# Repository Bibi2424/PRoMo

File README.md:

# PRoMo

## "Plateforme pour la Robotique Mobile"

### Mobile Robotic Plateform

This project is about creating a mobile robot from scratch.
There are four major parts in this project :

- Mechanics : Build a differential drive plateform with two DC motors with encoders. The different components must be build with Laser cutting and 3D printing (from low cost websites).
			
- Electronics : Create a main board based on a STM32F4 microcontroller with many components like motors, sensors, actuators, RF transmitters...
			
- Firmware : This can go two ways:
	- Provide a sets of high level librairies for controlling a sets of sensors and actuators and example projects, 
	- Give the code as is but with a performant way of interfacing with it (serial communication)

- Documentation : All the informations to understand the project will be there, with some tutorials. At the moment, used to store local datasheets
			
The aim of this projects is to propose some basics to start mobile robotic for the beginners and to simplify things for advanced people.

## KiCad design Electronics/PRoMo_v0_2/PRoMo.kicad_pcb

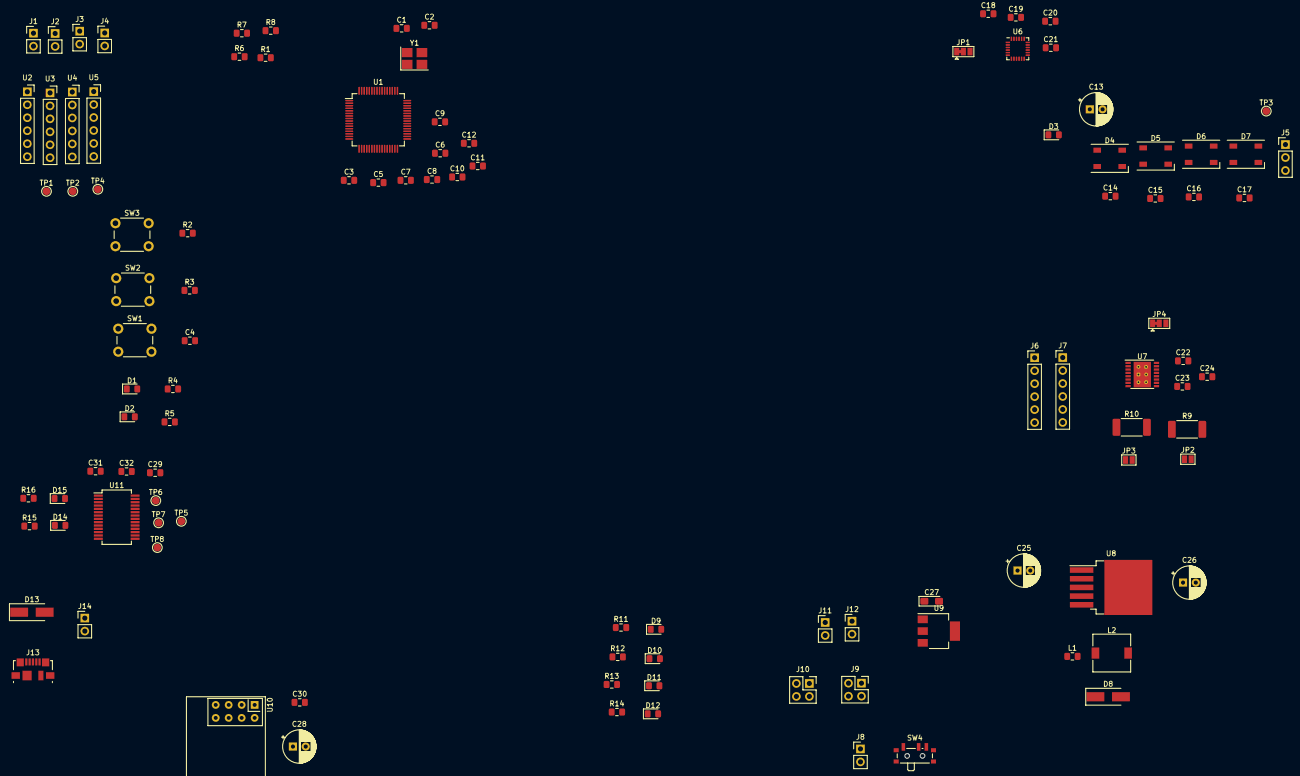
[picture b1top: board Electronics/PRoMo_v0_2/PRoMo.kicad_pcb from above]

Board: 2 copper layers, 111 parts (0 on the bottom side), 76 nets, no tracks yet.

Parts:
C1, C2: 18pF; C_0805_2012Metric_Pad1.15x1.40mm_HandSolder
C3, C4, C5, C7, C8, C9, C12, C14, C15, C16, C17, C19, C20, C29, C31: 100nF; C_0805_2012Metric_Pad1.15x1.40mm_HandSolder
C6, C32: 4.7uF; C_0805_2012Metric_Pad1.15x1.40mm_HandSolder
C10, C24: 10uF; C_0805_2012Metric_Pad1.15x1.40mm_HandSolder
C11: 1uF; C_0805_2012Metric_Pad1.15x1.40mm_HandSolder
C13, C28: 100uF; CP_Radial_D6.3mm_P2.50mm
C18, C22: 10nF; C_0805_2012Metric_Pad1.15x1.40mm_HandSolder
C21: 2.2nF; C_0805_2012Metric_Pad1.15x1.40mm_HandSolder
C23: 2.2uF; C_0805_2012Metric_Pad1.15x1.40mm_HandSolder
C25: 680uF; CP_Radial_D6.3mm_P2.50mm
C26: 220uF; CP_Radial_D6.3mm_P2.50mm
C27: 10uF; CP_EIA-3216-18_Kemet-A_Pad1.58x1.35mm_HandSolder
C30: Unpopulated; C_0805_2012Metric_Pad1.15x1.40mm_HandSolder
D1, D2: LED_Blue; LED_0805_2012Metric_Pad1.15x1.40mm_HandSolder
D3: M7; D_0805_2012Metric_Pad1.15x1.40mm_HandSolder
D4, D5, D6, D7: SK6812; LED_SK6812_PLCC4_5.0x5.0mm_P3.2mm
D8: SS14; D_SMA_Handsoldering
D9: LED_Red; LED_0805_2012Metric_Pad1.15x1.40mm_HandSolder
D10: LED_Yellow; LED_0805_2012Metric_Pad1.15x1.40mm_HandSolder
D11, D12: LED_Green; LED_0805_2012Metric_Pad1.15x1.40mm_HandSolder
D13: D_Zener_Small; D_SMA_Handsoldering
D14, D15: Yellow; LED_0805_2012Metric_Pad1.15x1.40mm_HandSolder
H1, H2, H3, H4: MountingHole; MountingHole_3.2mm_M3
J1, J2, J3, J4, J8, J14: Conn_01x02; PinHeader_1x02_P2.54mm_Vertical
J5: Conn_01x03; PinHeader_1x03_P2.54mm_Vertical
J6: ME_L; PinHeader_1x06_P2.54mm_Vertical
J7: ME_R; PinHeader_1x06_P2.54mm_Vertical
J9, J10: Conn_02x02_Counter_Clockwise; PinSocket_2x02_P2.54mm_Vertical
J11: AUX_IN; PinHeader_1x02_P2.54mm_Vertical
J12: AUX_OUT; PinHeader_1x02_P2.54mm_Vertical
J13: USB_B_Micro; USB_Micro-B_Molex_47346-0001
JP1: SLAVE_ADDR; SolderJumper-3_P1.3mm_Bridged12_Pad1.0x1.5mm
JP2, JP3: SolderJumper_2_Open; SolderJumper-2_P1.3mm_Open_Pad1.0x1.5mm
JP4: SolderJumper_3_Bridged12; SolderJumper-3_P1.3mm_Bridged12_Pad1.0x1.5mm
L1: 22uh; L_0805_2012Metric_Pad1.15x1.40mm_HandSolder
L2: 33uh; L_7.3x7.3_H3.5
R1, R6, R7, R8: 1k; R_0805_2012Metric_Pad1.15x1.40mm_HandSolder
R2, R3: 10k; R_0805_2012Metric_Pad1.15x1.40mm_HandSolder
R4, R5, R14: 47R; R_0805_2012Metric_Pad1.15x1.40mm_HandSolder
R9, R10: Sense; R_2512_6332Metric_Pad1.52x3.35mm_HandSolder
R11: 470R; R_0805_2012Metric_Pad1.15x1.40mm_HandSolder
R12: 330R; R_0805_2012Metric_Pad1.15x1.40mm_HandSolder
R13, R15, R16: 220R; R_0805_2012Metric_Pad1.15x1.40mm_HandSolder
SW1, SW2, SW3: DIP-BUTTON_2P-6.0X3.0X4.3MM_; SW_PUSH_6mm_H5mm
SW4: SW_SPDT; SW_SPDT_PCM12
TP1, TP2, TP3, TP4, TP5, TP6, TP7, TP8: TestPoint; TestPoint_Pad_D1.5mm
U1: STM32F401RETx; LQFP-64_10x10mm_P0.5mm
U2, U3, U4, U5: VL53l0x_breakout; PinSocket_1x06_P2.54mm_Vertical
U6: MPU-6050; InvenSense_QFN-24_4x4mm_P0.5mm
U7: DRV8833PWP; HTSSOP-16-1EP_4.4x5mm_P0.65mm_EP3.4x5mm_Mask2.46x2.31mm_The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
U8: LM2596S-5; TO-263-5_TabPin3
U9: AMS1117-3.3; SOT-223-3_TabPin2
U10: NRF24L01_Breakout; nRF24L01_Breakout
U11: FT232RL; SSOP-28_5.3x10.2mm_P0.65mm
Y1: Crystal_GND24; Crystal_SMD_3225-4Pin_3.2x2.5mm_HandSoldering

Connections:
+3V3: C3.1, C5.1, C7.1, C8.1, C9.2, C10.1, C11.1, C12.1, C18.2, C19.2, C27.1, C28.1, C30.1, J6.3, J7.3, J10.1, J10.2, JP1.3, R1.1, R2.2, R3.2, R4.1, R5.1, R6.1, R7.1, R8.1, R14.2, U1.13, U1.19, U1.32, U1.48, U1.64, U2.1, U3.1, U4.1, U5.1, U6.8, U6.13, U9.2, U10.2
+5V: C13.1, C15.1, C16.1, C17.1, C26.1, C31.2, C32.2, D3.2, D5.3, D6.3, D7.3, J5.1, J9.1, J9.2, J12.2, J14.1, L1.2, L2.2, R13.2, R15.1, R16.1, U8.4, U9.3, U11.4, U11.20
/BOOT1_BP2: R2.1, SW3.1, U1.28
/BP1: R3.1, SW2.1, U1.2
/LED_USR1: D1.1, U1.55
/LED_USR2: D2.1, U1.43
/Motor_driver/ML1: J6.1, U7.2
/Motor_driver/ML2: J6.2, U7.4
/Motor_driver/MR1: J7.1, U7.7
/Motor_driver/MR2: J7.2, U7.5
ADC_ML_SENSE: JP2.2, R9.1, U1.10, U7.3
ADC_MR_SENSE: JP3.2, R10.1, U1.11, U7.6
ADDR_LEDS: D4.2, U1.53
DRV_EN: JP4.1, U1.54
Encoder_L_A: J6.4, U1.56
Encoder_L_B: J6.5, U1.57
Encoder_R_A: J7.4, U1.58
Encoder_R_B: J7.5, U1.59
FTDI_RX: TP6.1, U11.1
FTDI_TX: TP7.1, U11.5
GND: C1.2, C2.2, C3.2, C4.2, C5.2, C6.2, C7.2, C8.2, C10.2, C11.2, C12.2, C13.2, C14.2, C15.2, C16.2, C17.2, C18.1, C19.1, C20.2, C21.2, C23.1, C24.2, C25.2, C26.2, C27.2, C28.2, C29.1, C30.2, C31.1, C32.1, D4.1, D5.1, D6.1, D7.1, D8.2, D9.1, D10.1, D11.1, D12.1, J1.2, J2.2, J3.2, J4.2, J5.3, J6.6, J7.6, J8.1, J9.3, J9.4, J10.3, J10.4, J11.1, J12.1, J13.5, JP1.1, JP2.1, JP3.1, R9.2, R10.2, SW1.1, SW2.2, SW3.2, U1.12, U1.18, U1.31, U1.47, U1.63, U2.2, U3.2, U4.2, U5.2, U6.18, U7.13, U7.17, U8.3, U8.5, U9.1, U10.1, U11.7, U11.18, U11.21, U11.25, Y1.2, Y1.4
I2C_AUX_SCL: R6.2, U1.41
I2C_AUX_SDA: R1.2, U1.40
MPU_INT: U1.8, U6.12
NRF_CE: U1.29, U10.3
NRF_IRQ: U1.9, U10.8
NRF_SPI_MISO: U1.35, U10.7
NRF_SPI_MOSI: U1.36, U10.6
NRF_SPI_SCK: U1.34, U10.5
NRF_nCSN: U1.33, U10.4
NRST: C4.1, JP4.3, SW1.2, U1.7
unnamed: C1.1, U1.5, Y1.1
unnamed: C2.1, U1.6, Y1.3
unnamed: C6.1, U1.30
unnamed: C9.1, U1.1
unnamed: C14.1, D3.1, D4.3
unnamed: C20.1, U6.10
unnamed: C21.1, U6.20
unnamed: C22.1, U7.11
unnamed: C23.2, U7.14
unnamed: C29.2, U11.17
unnamed: D1.2, R4.2
unnamed: D2.2, R5.2
unnamed: D4.4, D5.2
unnamed: D5.4, D6.2
unnamed: D6.4, D7.2
unnamed: D7.4, J5.2, TP3.1
unnamed: D8.1, L1.1, L2.1, U8.2
unnamed: D9.2, R11.1
unnamed: D10.2, R12.1
unnamed: D11.2, R13.1
unnamed: D12.2, R14.1
unnamed: D13.1, J14.2
unnamed: D14.1, U11.23
unnamed: D14.2, R15.2
unnamed: D15.1, U11.22
unnamed: D15.2, R16.2
unnamed: J8.2, SW4.2
unnamed: J13.2, U11.16
unnamed: J13.3, U11.15
unnamed: JP1.2, U6.9
unnamed: JP4.2, U7.1
unnamed: TP1.1, U3.5
unnamed: TP2.1, U4.5
unnamed: TP4.1, U5.5
unnamed: TP5.1, U11.19
unnamed: TP8.1, U11.2
VBAT: C22.2, C24.1, C25.1, J11.2, R11.2, SW4.3, U7.12, U8.1
VBUS: D13.2, J13.1, R12.2
VL53l0_1_INT: U1.50, U2.5
VL53l0_1_XSHUT: J1.1, U1.51, U2.6
VL53l0_2_XSHUT: J2.1, U1.52, U3.6
VL53l0_3_XSHUT: J3.1, U1.3, U4.6
VL53l0_4_XSHUT: J4.1, U1.4, U5.6
VL53l0_I2C_SCL: R7.2, U1.61, U2.3, U3.3, U4.3, U5.3
VL53l0_I2C_SDA: R8.2, U1.62, U2.4, U3.4, U4.4, U5.4

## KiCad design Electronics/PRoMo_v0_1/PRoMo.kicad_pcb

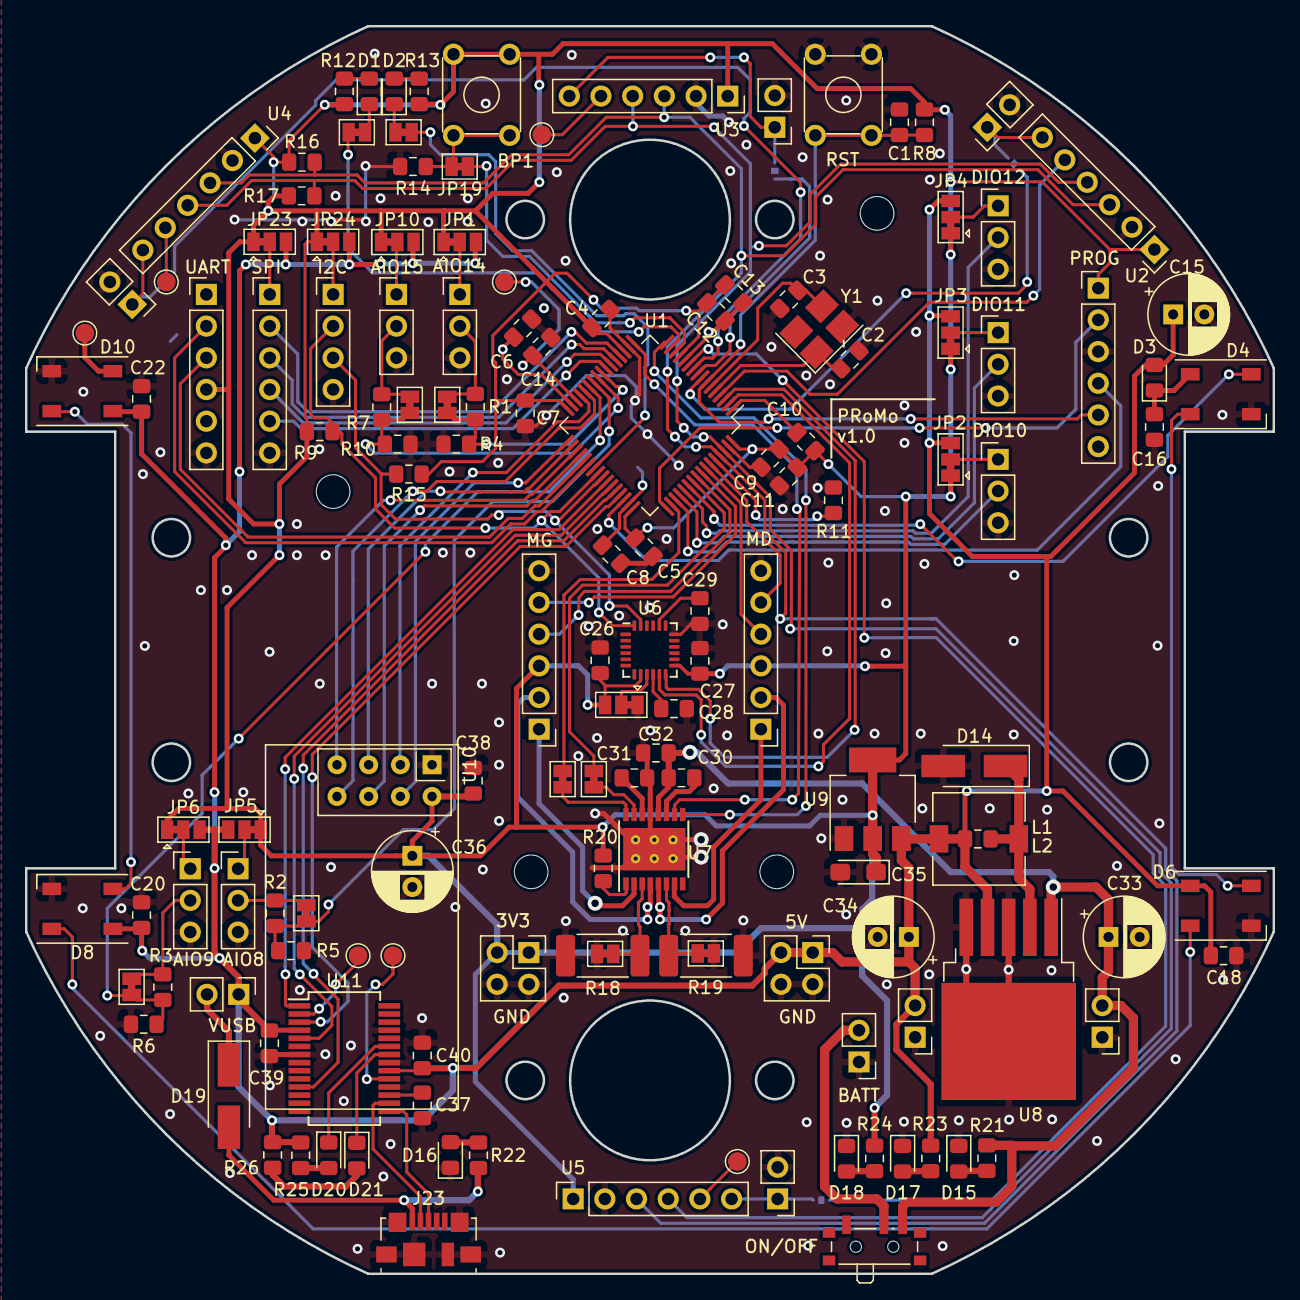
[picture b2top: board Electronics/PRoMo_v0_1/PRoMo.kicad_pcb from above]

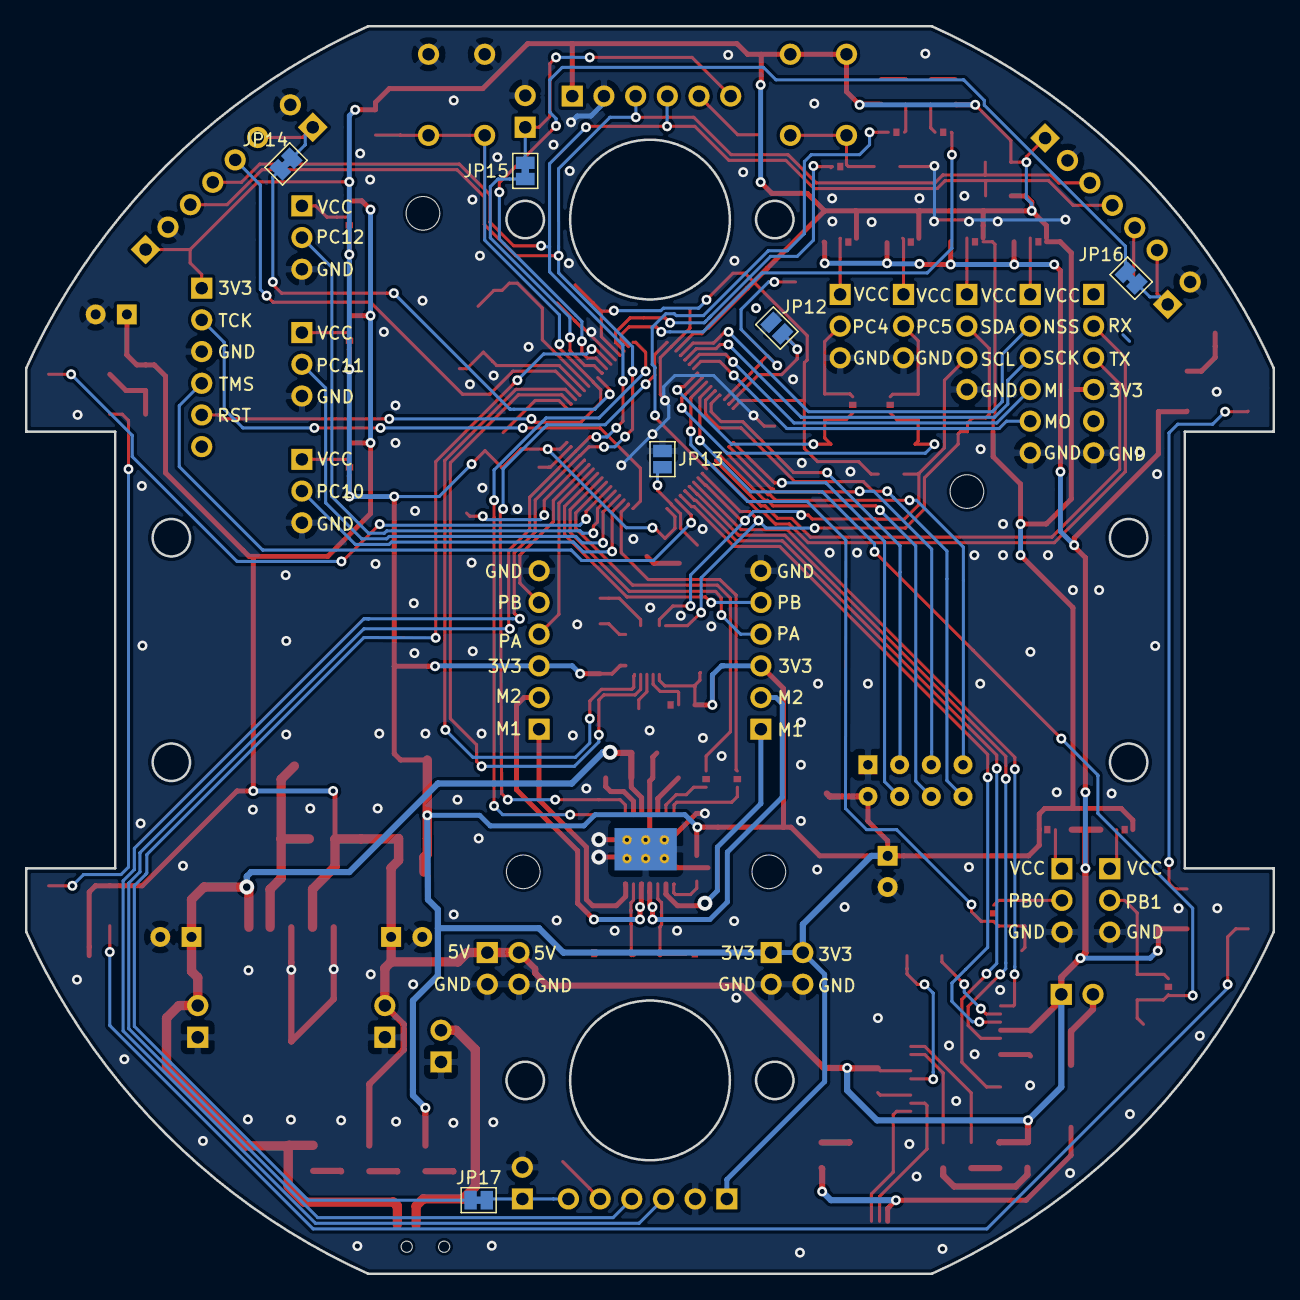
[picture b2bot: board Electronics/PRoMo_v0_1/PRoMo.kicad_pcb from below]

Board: 2 copper layers, 100.0 x 100.0 mm, 154 parts (6 on the bottom side), 121 nets.

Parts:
C1, C4, C5, C7, C9, C10, C13, C16, C18, C20, C22, C27, C28, C37, C39: 100nF; C_0805_2012Metric_Pad1.15x1.40mm_HandSolder
C2, C3: 18pF; C_0805_2012Metric_Pad1.15x1.40mm_HandSolder
C6, C8, C31: 2.2uF; C_0805_2012Metric_Pad1.15x1.40mm_HandSolder
C11, C32: 10uF; C_0805_2012Metric_Pad1.15x1.40mm_HandSolder
C12: 1uF; C_0805_2012Metric_Pad1.15x1.40mm_HandSolder
C14, C40: 4.7uF; C_0805_2012Metric_Pad1.15x1.40mm_HandSolder
C15, C36: 100uF; CP_Radial_D6.3mm_P2.50mm
C26, C30: 10nF; C_0805_2012Metric_Pad1.15x1.40mm_HandSolder
C29: 2.2nF; C_0805_2012Metric_Pad1.15x1.40mm_HandSolder
C33: 680uF; CP_Radial_D6.3mm_P2.50mm
C34: 220uF; CP_Radial_D6.3mm_P2.50mm
C35: 10uF; CP_EIA-3216-18_Kemet-A_Pad1.58x1.35mm_HandSolder
C38: Unpopulated; C_0805_2012Metric_Pad1.15x1.40mm_HandSolder
D1, D2: LED_Blue; LED_0805_2012Metric_Pad1.15x1.40mm_HandSolder
D3: M7; D_0805_2012Metric_Pad1.15x1.40mm_HandSolder
D4, D6, D8, D10: SK6812; LED_SK6812_PLCC4_5.0x5.0mm_P3.2mm
D14: SS14; D_SMA_Handsoldering
D15: LED_Red; LED_0805_2012Metric_Pad1.15x1.40mm_HandSolder
D16: LED_Yellow; LED_0805_2012Metric_Pad1.15x1.40mm_HandSolder
D17, D18: LED_Green; LED_0805_2012Metric_Pad1.15x1.40mm_HandSolder
D19: D_Zener_Small; D_SMA_Handsoldering
D20, D21: Yellow; LED_0805_2012Metric_Pad1.15x1.40mm_HandSolder
H1, H2, H3, H4: MountingHole; MountingHole_2.7mm_M2.5
J1: AN14; PinHeader_1x03_P2.54mm_Vertical
J2: GPIO1; PinHeader_1x03_P2.54mm_Vertical
J3: GPIO2; PinHeader_1x03_P2.54mm_Vertical
J4: GPIO3; PinHeader_1x03_P2.54mm_Vertical
J5: AN8; PinHeader_1x03_P2.54mm_Vertical
J6: AN9; PinHeader_1x03_P2.54mm_Vertical
J7: AN15; PinHeader_1x03_P2.54mm_Vertical
J8: Programming; PinHeader_1x06_P2.54mm_Vertical
J9: UART6_AUX; PinHeader_1x06_P2.54mm_Vertical
J10: SPI1_AUX; PinHeader_1x06_P2.54mm_Vertical
J11: I2C2_AUX; PinHeader_1x04_P2.54mm_Vertical
J12, J13, J14, J15, J18, J24: Conn_01x02; PinHeader_1x02_P2.54mm_Vertical
J16: ME_L; PinHeader_1x06_P2.54mm_Vertical
J17: ME_R; PinHeader_1x06_P2.54mm_Vertical
J19, J20: Conn_02x02_Counter_Clockwise; PinSocket_2x02_P2.54mm_Vertical
J21: AUX_IN; PinHeader_1x02_P2.54mm_Vertical
J22: AUX_OUT; PinHeader_1x02_P2.54mm_Vertical
J23: USB_B_Micro; USB_Micro-B_Molex_47346-0001
JP1, JP2, JP3, JP4, JP5, JP6, JP10, JP23, JP24: SolderJumper_3_Bridged12; SolderJumper-3_P1.3mm_Bridged12_Pad1.0x1.5mm
JP7, JP8, JP9, JP11, JP14, JP15, JP16, JP17, JP18, JP19, JP20, JP21, JP22, JP26, JP27: SolderJumper_2_Bridged; SolderJumper-2_P1.3mm_Bridged_Pad1.0x1.5mm
JP12, JP13: SolderJumper_2_Open; SolderJumper-2_P1.3mm_Open_Pad1.0x1.5mm
JP25: SLAVE_ADDR; SolderJumper-3_P1.3mm_Bridged12_Pad1.0x1.5mm
L1: 22uh; L_0805_2012Metric_Pad1.15x1.40mm_HandSolder
L2: 33uh; L_7.3x7.3_H3.5
R1, R2, R3, R4, R5, R6, R7, R9, R10, R15, R16, R17: 1k; R_0805_2012Metric_Pad1.15x1.40mm_HandSolder
R8: Unpopulated; R_0805_2012Metric_Pad1.15x1.40mm_HandSolder
R11, R14: 10k; R_0805_2012Metric_Pad1.15x1.40mm_HandSolder
R12, R13, R24: 47R; R_0805_2012Metric_Pad1.15x1.40mm_HandSolder
R18, R19: Sense; R_2512_6332Metric_Pad1.52x3.35mm_HandSolder
R20: 47k; R_0805_2012Metric_Pad1.15x1.40mm_HandSolder
R21: 470R; R_0805_2012Metric_Pad1.15x1.40mm_HandSolder
R22: 330R; R_0805_2012Metric_Pad1.15x1.40mm_HandSolder
R23, R25, R26: 220R; R_0805_2012Metric_Pad1.15x1.40mm_HandSolder
SW1: RESET_BP; SW_TH_Tactile_Omron_B3F-10xx
SW2: WKP_BP; SW_TH_Tactile_Omron_B3F-10xx
SW3: SW_SPDT; SW_SPDT_PCM12
TP1, TP2, TP3, TP4, TP5, TP6, TP7: TestPoint; TestPoint_Pad_D1.5mm
U1: STM32F405RGTx; LQFP-64_10x10mm_P0.5mm
U2, U3, U4, U5: VL53l0x_breakout; PinSocket_1x06_P2.54mm_Vertical
U6: MPU-6050; InvenSense_QFN-24_4x4mm_P0.5mm
U7: DRV8833PWP; HTSSOP-16-1EP_4.4x5mm_P0.65mm_EP3.4x5mm_Mask2.46x2.31mm_The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
U8: LM2596S-5; TO-263-5_TabPin3
U9: AMS1117-3.3; SOT-223-3_TabPin2
U10: NRF24L01_Breakout; nRF24L01_Breakout
U11: FT232RL; SSOP-28_5.3x10.2mm_P0.65mm
Y1: Crystal_GND24; Crystal_SMD_3225-4Pin_3.2x2.5mm_HandSoldering

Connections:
+3V3: C4.1, C5.1, C7.1, C9.1, C10.2, C11.1, C12.1, C13.1, C26.2, C27.2, C35.1, C36.1, C38.1, J8.1, J9.4, J16.3, J17.3, J20.1, J20.2, JP1.1, JP2.1, JP3.1, JP4.1, JP5.1, JP6.1, JP10.1, JP23.1, JP24.1, JP25.3, R8.1, R9.1, R12.1, R13.1, R15.1, R16.1, R17.1, R20.1, R24.2, SW2.2, SW2.4, U1.13, U1.19, U1.32, U1.48, U1.64, U2.1, U3.1, U4.1, U5.1, U6.8, U6.13, U9.2, U10.2
+5V: C15.1, C18.1, C20.1, C22.1, C34.1, C39.2, C40.2, D3.2, D6.3, D8.3, D10.3, J19.1, J19.2, J22.2, J24.1, JP1.3, JP2.3, JP3.3, JP4.3, JP5.3, JP6.3, JP10.3, JP23.3, JP24.3, L1.2, L2.2, R23.2, R25.1, R26.1, U8.4, U9.3, U11.4, U11.20
/LED_USR1: D1.1, JP20.2
/LED_USR2: D2.1, JP18.2
/Motor_driver/ML1: J16.1, U7.2
/Motor_driver/ML2: J16.2, U7.4
/Motor_driver/MR1: J17.1, U7.7
/Motor_driver/MR2: J17.2, U7.5
/NRST: C1.1, J8.5, R8.2, SW1.1, SW1.3, U1.7
/TCK: J8.2, U1.49
/TMS: J8.4, U1.46
ADC1_8: JP8.2, R2.1, R5.2, U1.26
ADC1_9: JP9.2, R3.1, R6.2, U1.27
ADC1_14: JP7.2, R1.1, R4.2, U1.24
ADC1_15: JP11.2, R7.1, R10.2, U1.25
ADDR_LEDS: D4.2, U1.54
Encoder_L_A: J16.4, U1.56
Encoder_L_B: J16.5, U1.57
Encoder_R_A: J17.4, U1.58
Encoder_R_B: J17.5, U1.59
FTDI_CTS: U1.44, U11.11
FTDI_RTS: U1.45, U11.3
FTDI_RX: U1.43, U11.5
FTDI_TX: U1.42, U11.1
GND: C1.2, C2.2, C3.2, C4.2, C5.2, C6.2, C7.2, C8.2, C9.2, C11.2, C12.2, C13.2, C14.2, C15.2, C16.2, C18.2, C20.2, C22.2, C26.1, C27.1, C28.2, C29.2, C31.1, C32.2, C33.2, C34.2, C35.2, C36.2, C37.1, C38.2, C39.1, C40.1, D4.1, D6.1, D8.1, D10.1, D14.2, D15.1, D16.1, D17.1, D18.1, J1.3, J2.3, J3.3, J4.3, J5.3, J6.3, J7.3, J8.3, J9.6, J10.6, J11.4, J12.2, J13.2, J14.2, J15.2, J16.6, J17.6, J18.1, J19.3, J19.4, J20.3, J20.4, J21.1, J22.1, J23.5, J23.6, JP12.2, JP13.2, JP25.1, JP26.1, JP27.1, R4.1, R5.1, R6.1, R10.1, R11.2, R14.1, R18.2, R19.2, SW1.2, SW1.4, U1.12, U1.18, U1.63, U2.2, U3.2, U4.2, U5.2, U6.18, U7.13, U7.17, U8.3, U8.5, U9.1, U10.1, U11.7, U11.18, U11.21, U11.25, Y1.2, Y1.4
I2C1_SCL: R16.2, U1.61, U2.3, U3.3, U4.3, U5.3
I2C1_SDA: R17.2, U1.62, U2.4, U3.4, U4.4, U5.4
I2C2_SCL: J11.3, R15.2, U1.41, U6.23
I2C2_SDA: J11.2, R9.2, U1.40, U6.24
ML_PWM_H: JP21.2, U7.16
ML_PWM_L: JP22.2, U7.15
MPU_FSYNC: U1.2, U6.11
MPU_INT: U1.3, U6.12
MR_PWM_H: U1.16, U7.9
MR_PWM_L: U1.17, U7.10
NRF_CE: U1.29, U10.3
NRF_IRQ: U1.28, U10.8
NRF_nCSN: U1.33, U10.4
unnamed: C2.1, U1.5, Y1.1
unnamed: C3.1, U1.6, Y1.3
unnamed: C6.1, JP12.1, U1.31
unnamed: C8.1, JP13.1, U1.47
unnamed: C10.1, U1.1
unnamed: C14.1, TP1.1, U1.30
unnamed: C16.1, D3.1, D4.3
unnamed: C28.1, U6.10
unnamed: C29.1, U6.20
unnamed: C30.1, U7.11
unnamed: C31.2, U7.14
unnamed: C37.2, U11.17
unnamed: D1.2, R12.2
unnamed: D2.2, R13.2
unnamed: D4.4, D6.2
unnamed: D6.4, D8.2
unnamed: D8.4, D10.2
unnamed: D10.4, TP7.1
unnamed: D14.1, L1.1, L2.1, U8.2
unnamed: D15.2, R21.1
unnamed: D16.2, R22.1
unnamed: D17.2, R23.1
unnamed: D18.2, R24.1
unnamed: D19.1, J24.2
unnamed: D20.1, U11.23
unnamed: D20.2, R25.2
unnamed: D21.1, U11.22
unnamed: D21.2, R26.2
unnamed: J1.1, JP1.2
unnamed: J1.2, JP7.1, R1.2
unnamed: J2.1, JP2.2
unnamed: J3.1, JP3.2
unnamed: J4.1, JP4.2
unnamed: J5.1, JP5.2
unnamed: J5.2, JP8.1, R2.2
unnamed: J6.1, JP6.2
unnamed: J6.2, JP9.1, R3.2
unnamed: J7.1, JP10.2
unnamed: J7.2, JP11.1, R7.2
unnamed: J10.1, JP23.2
unnamed: J11.1, JP24.2
unnamed: J18.2, SW3.2
unnamed: J23.2, U11.16
unnamed: J23.3, U11.15
unnamed: JP14.1, U1.8
unnamed: JP15.1, U1.9
unnamed: JP16.1, U1.10
unnamed: JP17.1, U1.11
unnamed: JP18.1, U1.39
unnamed: JP19.1, U1.14
unnamed: JP19.2, R14.2, SW2.1, SW2.3
unnamed: JP20.1, U1.15
unnamed: JP21.1, U1.50
unnamed: JP22.1, U1.55
unnamed: JP25.2, U6.9
unnamed: JP26.2, R18.1, U7.3
unnamed: JP27.2, R19.1, U7.6
unnamed: R11.1, U1.60
unnamed: R20.2, U7.1
unnamed: TP2.1, U3.5
unnamed: TP3.1, U4.5
unnamed: TP4.1, U5.5
unnamed: TP5.1, U11.19
unnamed: TP6.1, U11.2
SPI1_MISO: J10.4, U1.22
SPI1_MOSI: J10.5, U1.23
SPI1_NSS: J10.2, U1.20
SPI1_SCK: J10.3, U1.21
SPI2_MISO: U1.35, U10.7
SPI2_MOSI: U1.36, U10.6
SPI2_SCK: U1.34, U10.5
Servo1: J2.2, U1.51
Servo2: J3.2, U1.52
Servo3: J4.2, U1.53
UART6_RX: J9.2, U1.38
UART6_TX: J9.3, U1.37
VBAT: C30.2, C32.1, C33.1, J21.2, R21.2, SW3.3, U7.12, U8.1
VBUS: D19.2, J23.1, R22.2
VL53l0_1_INT: U1.4, U2.5
VL53l0_1_XSHUT: J12.1, JP14.2, U2.6
VL53l0_2_XSHUT: J13.1, JP15.2, U3.6
VL53l0_3_XSHUT: J14.1, JP16.2, U4.6
VL53l0_4_XSHUT: J15.1, JP17.2, U5.6

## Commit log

2013-09-22 Premier commit : Ajout des ressources
    Ce premier commit consiste a rassembler tous les documents concernant ce
    projet.
2013-09-22 Avancement de la carte de base
2013-10-01 Choix des pins et début du routage
2014-06-18 Utilisation Lib SeeedStudio
2014-06-21 Schématique OK, début routage
2015-06-01 Routage done, mais revoir schématique
2016-11-15 Clean Up and Add start for 3D
2016-11-15 Finish cleaning and add create base for Eagle files
2018-10-27 Switch for PIC to ARM, basic project start
    Based on STM32F411RE Nucleo board, basic functions and basic encoder
    code working
2018-10-27 Give some love to this old project, re-define the scope of it
2018-10-28 Add motor basic support, switch to proto shield
2018-10-31 Improve Makefile and basic UART rx
2020-10-27 Move to Kicad and schematic Design almost done
2020-11-01 Schematic update and placement DONE
2020-11-07 Routing Done, All files ready for ordering
2020-11-20 Prepare Electronics v0.2, Add ballcaster holder file
2021-02-14 Small update to schematic and todo
2021-02-20 Remove Firmware code from main repo, will be added as submodule
2021-02-20 Add back the Firmware from submodule
2021-02-20 Some cleanup on the README
2021-02-23 Update License to MIT
2021-02-23 Bring Firmware up to speed
2021-02-23 Update firmware
2021-09-11 Start working on HW v0.2
2022-03-05 Update firmware submodule
2025-02-23 Update fw
